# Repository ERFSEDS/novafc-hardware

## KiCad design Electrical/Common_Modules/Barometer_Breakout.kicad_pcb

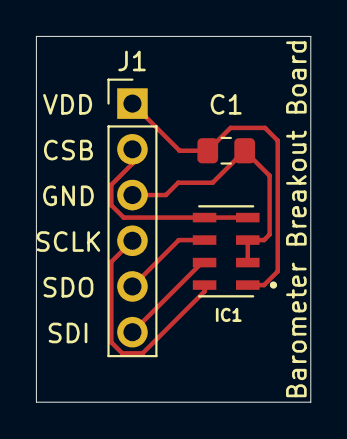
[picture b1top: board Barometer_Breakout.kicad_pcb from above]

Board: 2 copper layers, 15.2 x 20.3 mm, 3 parts (0 on the bottom side), 6 nets.

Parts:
C1: 100nF; C_0805_2012Metric_Pad1.15x1.40mm_HandSolder
IC1: MS560702BA03-50; SON125P300X500X100-8N
J1: Conn_01x06_Male; PinHeader_1x06_P2.54mm_Vertical

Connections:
unnamed: C1.1, IC1.2, IC1.3, J1.3
unnamed: C1.2, IC1.1, J1.1
unnamed: IC1.4, IC1.5, J1.2
unnamed: IC1.8, J1.4
unnamed: IC1.6, J1.5
unnamed: IC1.7, J1.6

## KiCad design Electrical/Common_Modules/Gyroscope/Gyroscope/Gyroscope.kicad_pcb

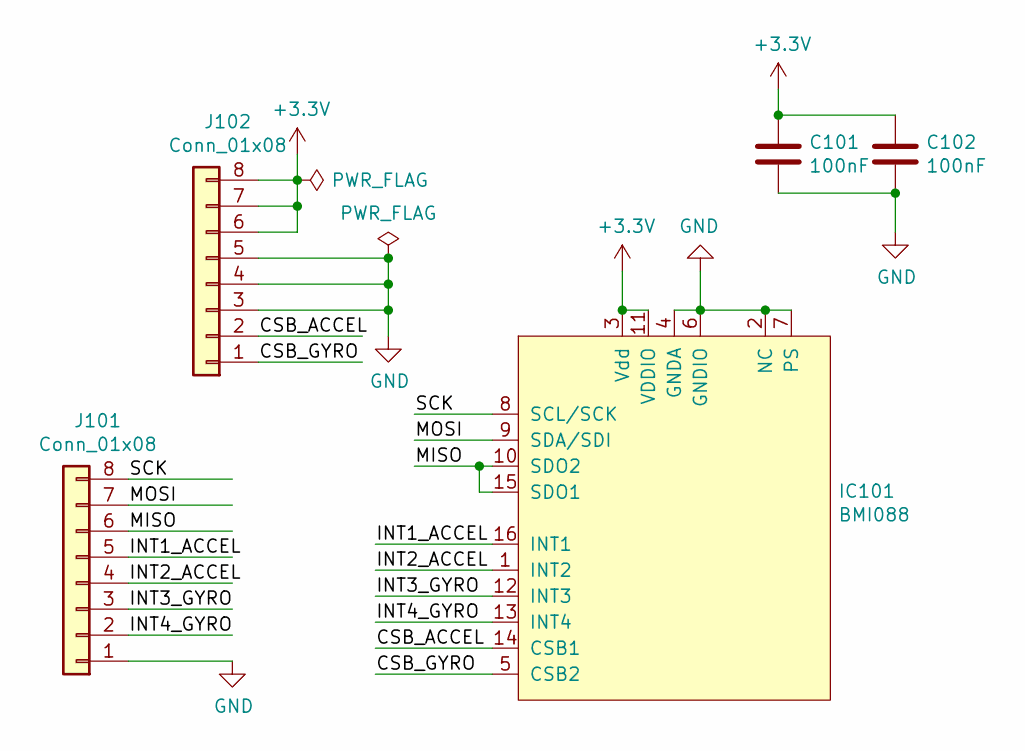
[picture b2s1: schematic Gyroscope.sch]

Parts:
C101, C102: 100nF; C_0201_0603Metric; digikey 490-6138-1-ND
IC101: BMI088; 16-LGA-(4.5x3); digikey 828-1082-1-ND
J101, J102: Conn_01x08; PinHeader_1x08_P2.54mm_Vertical; digikey 1988-1163-ND

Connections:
+3V3: C101.2, C102.2, IC101.3 (Vdd), IC101.11 (VDDIO), J102.6, J102.7, J102.8
/CSB_ACCEL: IC101.14 (CSB1), J102.2
/CSB_GYRO: IC101.5 (CSB2), J102.1
/INT1_ACCEL: IC101.16 (INT1), J101.5
/INT2_ACCEL: IC101.1 (INT2), J101.4
/INT3_GYRO: IC101.12 (INT3), J101.3
/INT4_GYRO: IC101.13 (INT4), J101.2
/MISO: IC101.10 (SDO2), IC101.15 (SDO1), J101.6
/MOSI: IC101.9 (SDA/SDI), J101.7
/SCK: IC101.8 (SCL/SCK), J101.8
GND: C101.1, C102.1, IC101.2 (NC), IC101.4 (GNDA), IC101.6 (GNDIO), IC101.7 (PS), J101.1, J102.3, J102.4, J102.5

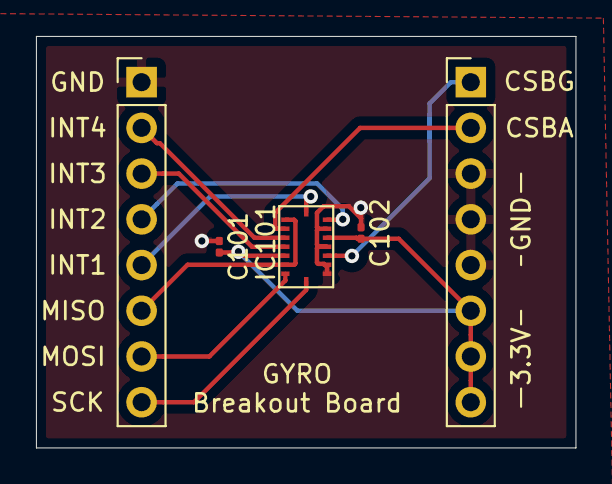
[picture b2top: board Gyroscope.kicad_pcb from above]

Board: 2 copper layers, 30.0 x 22.9 mm, 5 parts (0 on the bottom side), 11 nets.

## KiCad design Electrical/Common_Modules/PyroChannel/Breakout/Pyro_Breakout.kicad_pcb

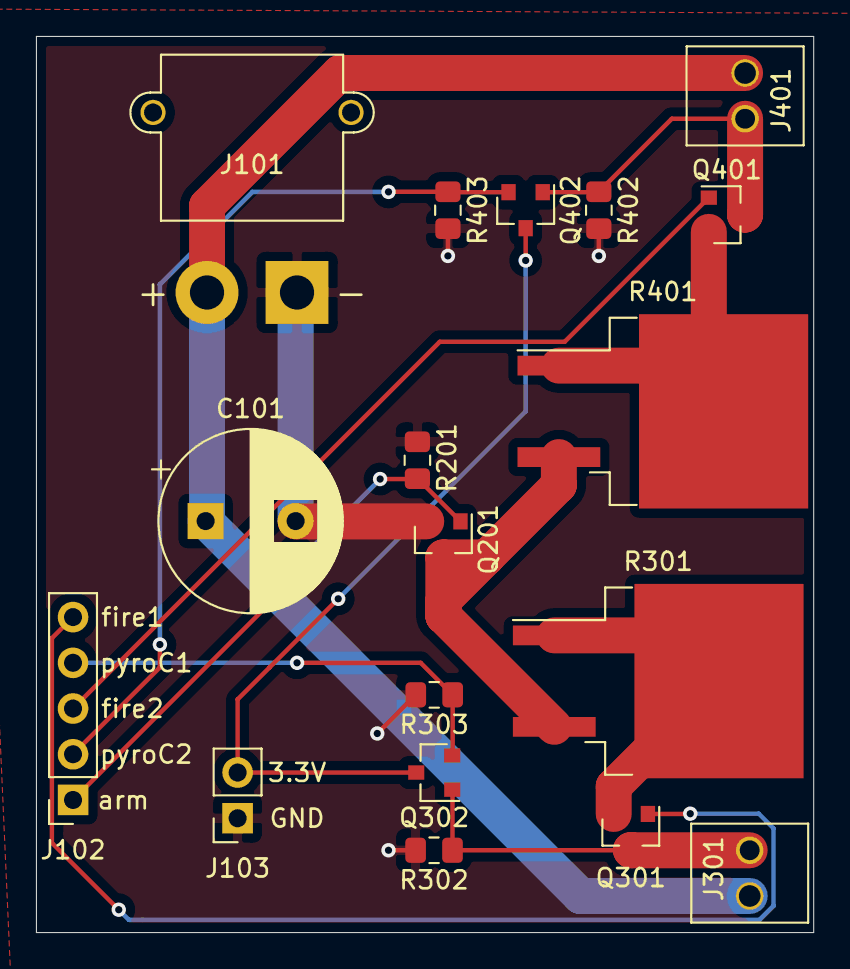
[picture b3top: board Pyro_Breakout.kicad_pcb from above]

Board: 2 copper layers, 43.2 x 49.8 mm, 18 parts (0 on the bottom side), 13 nets.

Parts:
C101: 1mF; CP_Radial_D10.0mm_P5.00mm
J101: Conn_01x02; AMASS_XT30PW-M_1x02_P2.50mm_Horizontal
J102: Conn_01x05; PinSocket_1x05_P2.54mm_Vertical
J103: Conn_01x02; PinSocket_1x02_P2.54mm_Vertical
J301, J401: Conn_01x02_Female; 2_pin_screw_terminal
Q201, Q301, Q302, Q401, Q402: IRLML6344TRPBFee; SOT-23
R201, R302, R303, R402, R403: 10k; R_0805_2012Metric_Pad1.15x1.40mm_HandSolder
R301, R401: 3.3; TO-263-2_TabPin1

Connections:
+3V3: J103.2, Q302.3, Q402.3
+BATT: C101.1, J101.2, J301.1, J401.1
/ArmSchematic/FireOut: Q201.3, R301.2, R401.2
/arm: J102.1, Q201.1, R201.1
/fire1: J102.5, Q301.1
/fire2: J102.3, Q401.1
/pyroCorrect1: J102.4, Q302.2, R303.1
/pyroCorrect2: J102.2, Q402.2, R403.1
GND: C101.2, J101.1, J103.1, Q201.2, R201.2, R302.2, R303.2, R402.2, R403.2
unnamed: J301.2, Q301.3, Q302.1, R302.1
unnamed: J401.2, Q401.3, Q402.1, R402.1
unnamed: Q301.2, R301.1
unnamed: Q401.2, R401.1
